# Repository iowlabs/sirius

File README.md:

# sirius
proyect to loraWAN PM sensor

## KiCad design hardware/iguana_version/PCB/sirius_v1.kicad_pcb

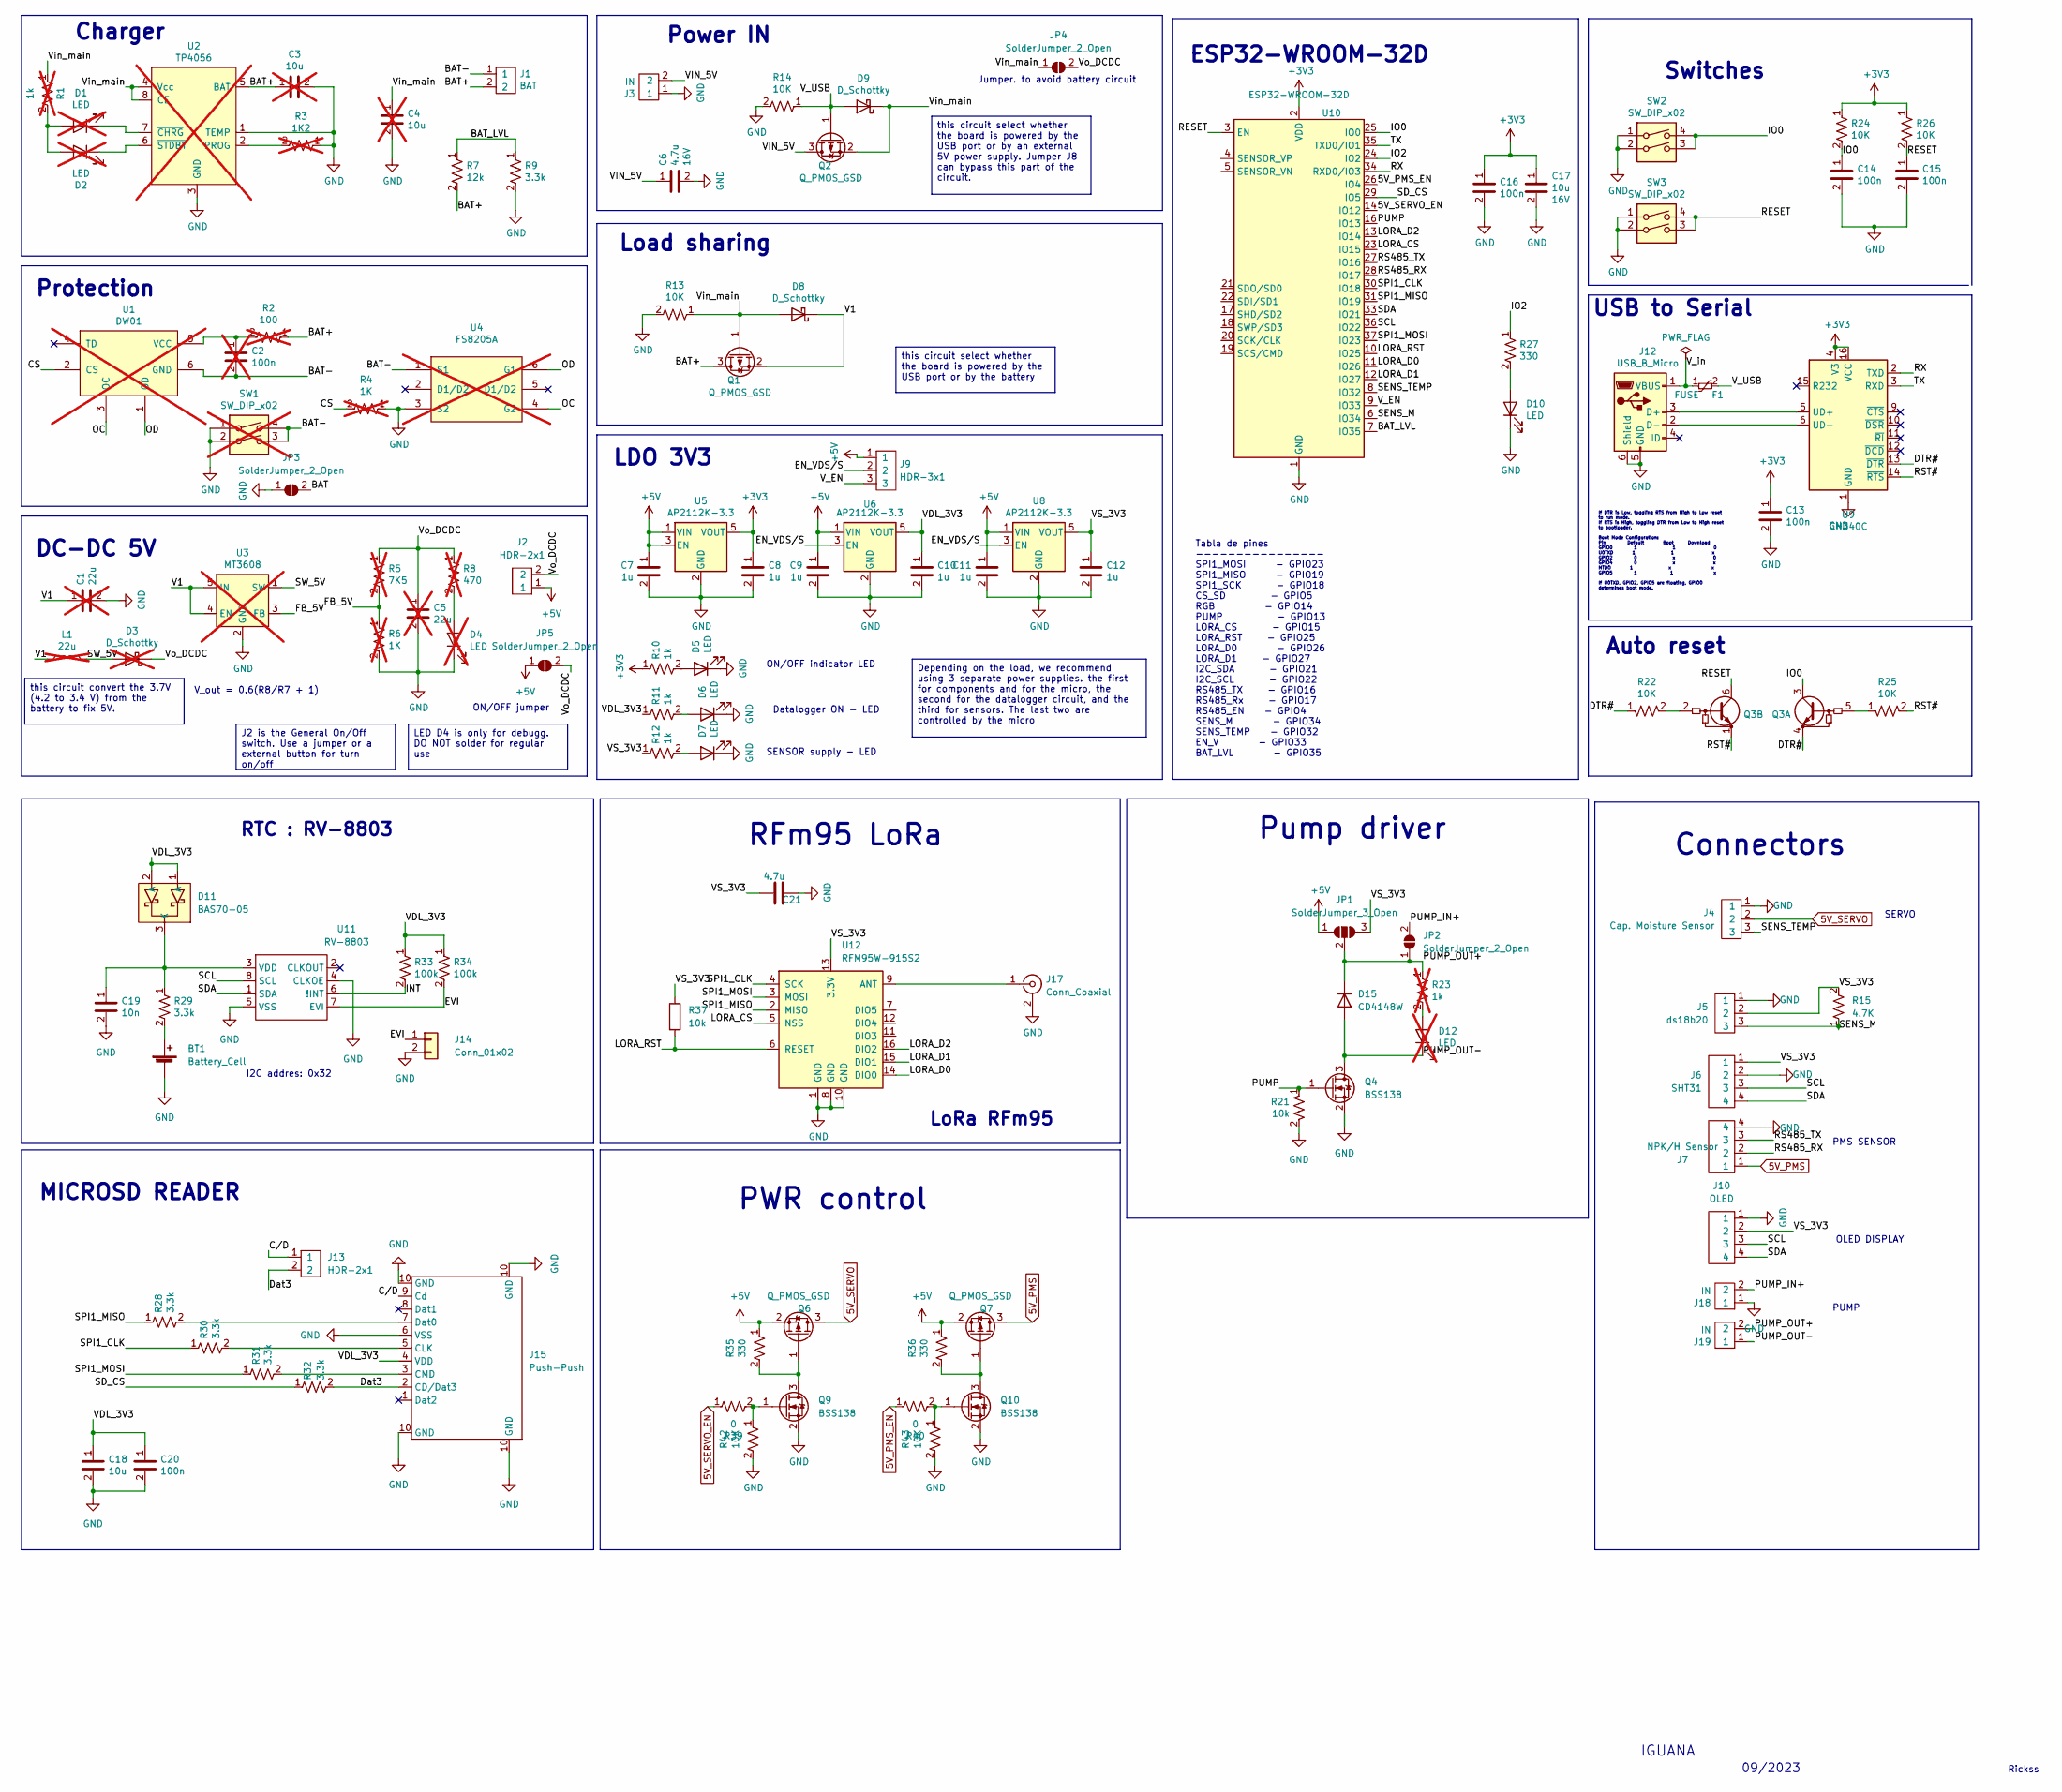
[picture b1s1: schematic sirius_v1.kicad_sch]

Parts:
BT1: Battery_Cell; BatteryHolder_Keystone_3000_1x12mm
C1, C5: 22u; C_0805_2012Metric; Voltage rated 16V; not fitted
C2: 100n; C_0603_1608Metric; Voltage rated 16V; not fitted
C3, C4: 10u; C_0805_2012Metric; Voltage rated 16V; not fitted
C6: 4.7u; C_0805_2012Metric; Voltage rated 16V
C7, C8, C9, C10, C11, C12: 1u; C_0603_1608Metric; Voltage rated 16V
C13, C14, C15, C16, C20: 100n; C_0603_1608Metric; Voltage rated 16V
C17, C18: 10u; C_0805_2012Metric; Voltage rated 16V
C19: 10n; C_0603_1608Metric; Voltage rated 16V
C21: 4.7u; C_0805_2012Metric
D1, D2, D4, D12: LED; LED_0603_1608Metric; not fitted
D3: D_Schottky; D_SMA; not fitted
D5, D6, D7, D10: LED; LED_0603_1608Metric
D8, D9: D_Schottky; D_SMA
D11: BAS70-05; SOT-23
D15: CD4148W; D_0805_2012Metric
F1: FUSE; Fuse_1206_3216Metric
J1: BAT; JST_XH_B2B-XH-A_1x02_P2.50mm_Vertical
J2: HDR-2x1; PinHeader_1x02_P2.54mm_Vertical
J3, J18, J19: IN; JST_XH_B2B-XH-A_1x02_P2.50mm_Vertical
J4: Cap. Moisture Sensor; JST_XH_B3B-XH-A_1x03_P2.50mm_Vertical
J5: ds18b20; JST_XH_B3B-XH-A_1x03_P2.50mm_Vertical
J6: SHT31; JST_XH_B4B-XH-A_1x04_P2.50mm_Vertical
J7: NPK/H Sensor; JST_XH_B4B-XH-A_1x04_P2.50mm_Vertical
J9: HDR-3x1; SolderJumper-3_P1.3mm_Open_RoundedPad1.0x1.5mm_NumberLabels
J10: OLED; JST_XH_B4B-XH-A_1x04_P2.50mm_Vertical
J12: USB_B_Micro; USB_Micro-B_Amphenol_10118194_Horizontal
J13: HDR-2x1; SolderJumper-2_P1.3mm_Open_RoundedPad1.0x1.5mm
J14: Conn_01x02; SolderJumper-2_P1.3mm_Open_RoundedPad1.0x1.5mm
J15: microSD_push_push
J17: Conn_Coaxial; U.FL_Molex_MCRF_73412-0110_Vertical
JP1: SolderJumper_3_Open; SolderJumper-3_P1.3mm_Open_RoundedPad1.0x1.5mm
JP2, JP3, JP4, JP5: SolderJumper_2_Open; SolderJumper-2_P1.3mm_Open_RoundedPad1.0x1.5mm
L1: 22u; L_Bourns_SRP7028A_7.3x6.6mm; not fitted
Q1, Q2, Q6, Q7: Q_PMOS_GSD; SOT-23
Q3: Q_Dual_NPN_NPN_BRT_E1B1C2E2B2C1; SOT-363_SC-70-6_Handsoldering
Q4, Q9, Q10: BSS138; SOT-23
R1, R23: 1k; R_0603_1608Metric; not fitted
R2: 100; R_0603_1608Metric; not fitted
R3: 1K2; R_0603_1608Metric; not fitted
R4, R6: 1K; R_0603_1608Metric; not fitted
R5: 7K5; R_0603_1608Metric; not fitted
R7: 12k; R_0603_1608Metric
R8: 470; R_0603_1608Metric; not fitted
R9, R28, R29, R30, R31, R32: 3.3k; R_0603_1608Metric
R10, R11, R12: 1k; R_0603_1608Metric
R13, R14, R22, R24, R25, R26, R42, R43: 10K; R_0603_1608Metric
R15: 4.7K; R_0603_1608Metric
R21, R37: 10k; R_0603_1608Metric
R27, R35, R36: 330; R_0603_1608Metric
R33, R34: 100k; R_0603_1608Metric
R39, R40: 0; R_0603_1608Metric
SW1: SW_DIP_x02; SMD_SWITCH; not fitted
SW2, SW3: SW_DIP_x02; SMD_SWITCH
U1: DW01; SOT-23-6; not fitted
U2: TP4056; TP4056_SOP-8-PP; not fitted
U3: MT3608; SOT-23-6; not fitted
U4: FS8205A; SOT-23-6; not fitted
U5, U6, U8: AP2112K-3.3; SOT-23-5
U9: CH340C; SOIC-16_3.9x9.9mm_P1.27mm
U10: ESP32-WROOM-32D; ESP32-WROOM-32
U11: RV-8803; SON-8
U12: RFM95W-915S2; HOPERF_RFM9XW_SMD

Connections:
5V_PMS: J7.1, Q7.3 (D)
5V_PMS_EN: R40.1, U10.26 (IO4)
5V_SERVO: J4.2, Q6.3 (D)
5V_SERVO_EN: R39.1, U10.14 (IO12)
+3V3: C8.1, C13.1, C16.1, C17.1, R10.1, R24.1, R26.1, U5.5 (VOUT), U9.4 (V3), U9.16 (VCC), U10.2 (VDD)
+5V: C7.1, C9.1, C11.1, J2.1, J9.1, JP1.1 (A), JP5.1 (A), Q6.2 (S), Q7.2 (S), R35.1, R36.1, U5.1 (VIN), U5.3 (EN), U6.1 (VIN), U8.1 (VIN)
/BAT+: C3.1, J1.2, Q1.3 (D), R2.1, R7.2, U2.5 (BAT)
/BAT-: C2.2, J1.1, JP3.2 (B), SW1.3, SW1.4, U1.6 (GND), U4.1 (S1)
/BAT_LVL: R7.1, R9.1, U10.7 (IO35)
/CS: R4.2, U1.2 (CS)
/C/D: J13.1, J15.9 (Cd)
/DTR#: Q3.4 (E1), R22.1, U9.13 (~DTR)
/Dat3: J13.2, J15.2 (CD/Dat3), R32.2
/EN_VDS/S: J9.2, U6.3 (EN), U8.3 (EN)
/EVI: J14.1, R34.2, U11.7 (EVI)
/FB_5V: R5.2, R6.1, U3.3 (FB)
/INT: R33.2, U11.6 (!INT)
/IO0: C14.1, Q3.3 (C1), R24.2, SW2.3, SW2.4, U10.25 (IO0)
/IO2: R27.1, U10.24 (IO2)
/LORA_CS: U10.23 (IO15), U12.5 (NSS)
/LORA_D0: U10.11 (IO26), U12.14 (DIO0)
/LORA_D1: U10.12 (IO27), U12.15 (DIO1)
/LORA_D2: U10.13 (IO14), U12.16 (DIO2)
/LORA_RST: R37.2, U10.10 (IO25), U12.6 (RESET)
/OC: U1.3 (OC), U4.4 (G2)
/OD: U1.1 (OD), U4.6 (G1)
/PUMP: Q4.1 (G), R21.1, U10.16 (IO13)
/PUMP_IN+: J18.2, JP2.2 (B)
/PUMP_OUT+: D15.1 (K), J19.2, JP1.2 (C), JP2.1 (A), R23.1
/PUMP_OUT-: D12.1 (K), D15.2 (A), J19.1, Q4.3 (D)
/RESET: C15.1, Q3.6 (C1), R26.2, SW3.3, SW3.4, U10.3 (EN)
/RS485_RX: J7.2, U10.28 (IO17)
/RS485_TX: J7.3, U10.27 (IO16)
/RST#: Q3.1 (E1), R25.2, U9.14 (~RTS)
/RX: U9.2 (TXD), U10.34 (RXD0/IO3)
/SCL: J6.3, J10.3, U10.36 (IO22), U11.8 (SCL)
/SDA: J6.4, J10.4, U10.33 (IO21), U11.1 (SDA)
/SD_CS: R32.1, U10.29 (IO5)
/SENS_M: J5.3, R15.1, U10.6 (IO34)
/SENS_TEMP: J4.3, U10.8 (IO32)
/SPI1_CLK: R30.1, U10.30 (IO18), U12.4 (SCK)
/SPI1_MISO: R28.1, U10.31 (IO19), U12.2 (MISO)
/SPI1_MOSI: R31.1, U10.37 (IO23), U12.3 (MOSI)
/SW_5V: D3.2 (A), L1.2, U3.1 (SW)
/TX: U9.3 (RXD), U10.35 (TXD0/IO1)
/V1: C1.1, D8.1 (K), L1.1, Q1.2 (S), U3.4 (EN), U3.5 (IN)
/VDL_3V3: C10.1, C18.1, C20.1, D11.1 (A), D11.2 (A), J15.4 (VDD), R11.1, R33.1, R34.1, U6.5 (VOUT)
/VIN_5V: C6.1, J3.2, Q2.3 (D)
/VS_3V3: C12.1, C21.2, J5.2, J6.1, J10.2, JP1.3 (B), R12.1, R15.2, R37.1, U8.5 (VOUT), U12.13 (3.3V)
/V_EN: J9.3, U10.9 (IO33)
/V_USB: D9.2 (A), F1.2, Q2.1 (G), R14.1
/V_in: F1.1, J12.1 (VBUS)
/Vin_main: C4.1, D8.2 (A), D9.1 (K), JP4.1 (A), Q1.1 (G), Q2.2 (S), R1.1, R13.1, U2.4 (Vcc), U2.8 (CE)
/Vo_DCDC: C5.1, D3.1 (K), J2.2, JP4.2 (B), JP5.2 (B), R5.1, R8.1
GND: BT1.2 (-), C1.2, C3.2, C4.2, C5.2, C6.2, C7.2, C8.2, C9.2, C10.2, C11.2, C12.2, C13.2, C14.2, C15.2, C16.2, C17.2, C18.2, C19.2, C20.2, C21.1, D4.1 (K), D5.1 (K), D6.1 (K), D7.1 (K), D10.1 (K), J3.1, J4.1, J5.1, J6.2, J7.4, J10.1, J12.5 (GND), J12.6 (Shield), J14.2, J15.6 (VSS), J15.10 (GND), J17.2 (Ext), J18.1, JP3.1 (A), Q4.2 (S), Q9.2 (S), Q10.2 (S), R3.1, R4.1, R6.2, R9.2, R13.2, R14.2, R21.2, R42.2, R43.2, SW1.1, SW1.2, SW2.1, SW2.2, SW3.1, SW3.2, U2.1 (TEMP), U2.3 (GND), U3.2 (GND), U4.3 (S2), U5.2 (GND), U6.2 (GND), U8.2 (GND), U9.1 (GND), U10.1 (GND), U10.15 (GND), U10.38 (GND), U10.39 (GND), U11.4 (CLKOE), U11.5 (VSS), U12.1 (GND), U12.8 (GND), U12.10 (GND)
unnamed: BT1.1 (+), R29.2
unnamed: D1.2 (A), D2.2 (A), R1.2
unnamed: D1.1 (K), U2.7 (~CHRG)
unnamed: D2.1 (K), U2.6 (~STDBY)
unnamed: D4.2 (A), R8.2
unnamed: D5.2 (A), R10.2
unnamed: D6.2 (A), R11.2
unnamed: D7.2 (A), R12.2
unnamed: D10.2 (A), R27.2
unnamed: C19.1, D11.3 (K), R29.1, U11.3 (VDD)
unnamed: D12.2 (A), R23.2
unnamed: J12.3 (D+), U9.5 (UD+)
unnamed: J12.2 (D-), U9.6 (UD-)
unnamed: J15.5 (CLK), R30.2
unnamed: J15.3 (CMD), R31.2
unnamed: J15.7 (Dat0), R28.2
unnamed: J17.1 (In), U12.9 (ANT)
unnamed: Q3.5 (B1), R25.1
unnamed: Q3.2 (B1), R22.2
unnamed: Q6.1 (G), Q9.3 (D), R35.2
unnamed: Q9.1 (G), R39.2, R42.1
unnamed: Q7.1 (G), Q10.3 (D), R36.2
unnamed: Q10.1 (G), R40.2, R43.1
unnamed: C2.1, R2.2, U1.5 (VCC)
unnamed: R3.2, U2.2 (PROG)

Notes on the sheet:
I2C addres: 0x32
DC-DC 5V
Tabla de pines ---------------- SPI1_MOSI - GPIO23 SPI1_MISO - GPIO19 SPI1_SCK - GPIO18 CS_SD - GPIO5 RGB - GPIO14 PUMP - GPIO13 LORA_CS - GPIO15 LORA_RST - GPIO25 LORA_D0 - GPIO26 LORA_D1 - GPIO27 I2C_SDA - GPIO21 I2C_SCL - GPIO22 RS485_TX - GPIO16 RS485_Rx - GPIO17 RS485_EN - GPIO4 SENS_M - GPIO3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
ON/OFF indicator LED
Power IN
RTC : RV-8803
Auto reset
ON/OFF jumper
USB to Serial
Connectors
PUMP
IGUANA
MICROSD READER
09/2023
Jumper. to avoid battery circuit
If DTR is Low, toggling RTS from High to Low reset to run mode. If RTS is High, toggling DTR from Low to High reset to bootloader. Boot Mode Configuration: Pin Default Boot Download GPIO0 1 1 0 U0TXD 1 1 x GPIO2 0 x 0 GPIO4 0 x x MTDO 1 x x GPIO5 1 1 x If U0TXD, GPIO2, GPIO5 are floating, GPIO0 det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
PWR control
Load sharing
ESP32-WROOM-32D
RFm95 LoRa
Pump driver
Charger
Switches
LoRa RFm95
SERVO
Rickss
V_out = 0.6(R8/R7 + 1)
SENSOR supply - LED
Protection
Datalogger ON - LED
OLED DISPLAY
PMS SENSOR
LDO 3V3
this circuit select whether the board is powered by the USB port or by the battery
this circuit select whether the board is powered by the USB port or by an external 5V power supply. Jumper J8 can bypass this part of the circuit.
LED D4 is only for debugg. DO NOT solder for regular use
this circuit convert the 3.7V (4.2 to 3.4 V) from the battery to fix 5V.
J2 is the General On/Off switch. Use a jumper or a external button for turn on/off
Depending on the load, we recommend using 3 separate power supplies. the first for components and for the micro, the second for the datalogger circuit, and the third for sensors. The last two are controlled by the micro

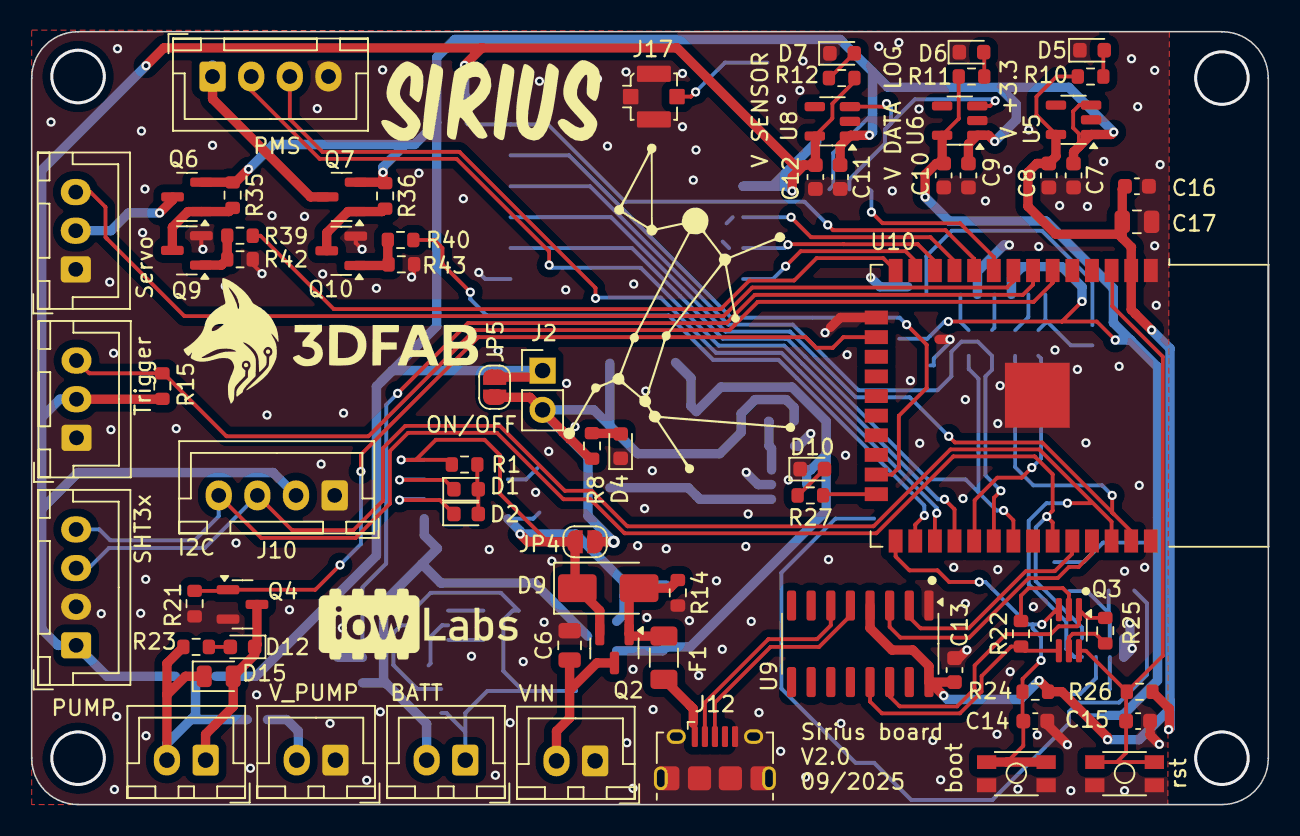
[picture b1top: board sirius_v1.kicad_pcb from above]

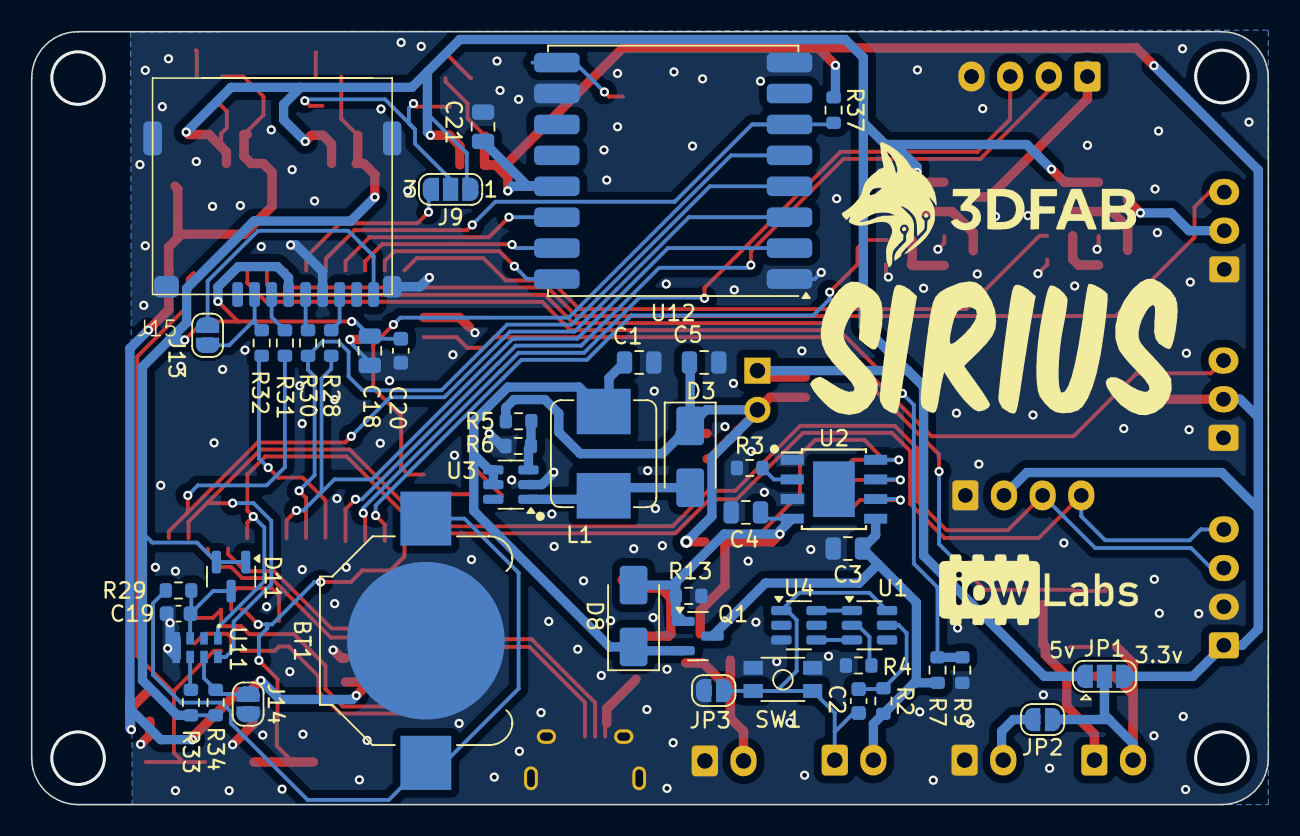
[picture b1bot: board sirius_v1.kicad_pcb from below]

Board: 2 copper layers, 80.0 x 50.0 mm, 116 parts (45 on the bottom side), 80 nets.

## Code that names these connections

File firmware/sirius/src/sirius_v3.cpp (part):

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

//PINES
#define SD_CS   5
#define MISO    19
#define MOSI    23
#define CLK     18
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
#define PMS_EN_PIN 4
#define SERVO_EN_PIN 12
#define V_EN	33
#define BAM_EN	13

#define LORA_D0 26
#define LORA_D1 27
#define LORA_D2 14
#define LORA_CS 15
#define LORA_RST 25



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	#define PMS_EN_PIN 4
	#define SERVO_EN_PIN 12

	pinMode(SD_CS, OUTPUT);
	pinMode(V_EN,  OUTPUT); 	//enable power to sd and others
	pinMode(PMS_EN_PIN,OUTPUT);
	pinMode(SERVO_EN_PIN,OUTPUT);
	pinMode(MODE_SWITCH, INPUT);
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
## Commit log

2025-08-02 adding test fot otaa and abp
2025-08-19 fixing to add real value of variables to payload
2025-09-02 adding pcb and gerber files of iguana and sirius version
2025-09-02 updating bom
2025-11-21 code updating upto node 12 and add sensor AHT10 capabilities
2025-11-21 adding botton feature
2026-05-25 updating fab files
2026-06-03 changes on bom
2026-06-03 test signed commit
